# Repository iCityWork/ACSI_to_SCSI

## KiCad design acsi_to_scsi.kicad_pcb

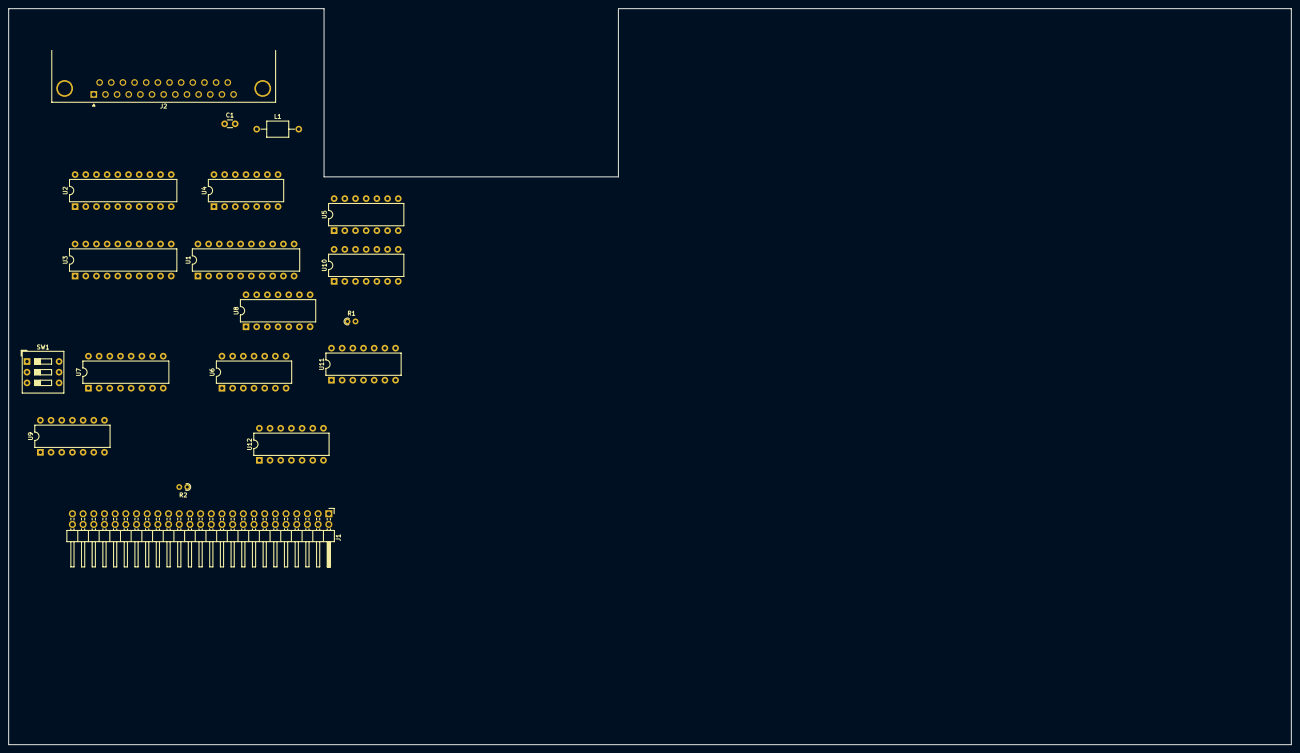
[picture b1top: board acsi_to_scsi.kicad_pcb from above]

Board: 2 copper layers, 305.0 x 175.0 mm, 19 parts (0 on the bottom side), 64 nets, no tracks yet.

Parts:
C1: 27pF; C_Disc_D3.0mm_W1.6mm_P2.50mm
J1: SCSI; PinHeader_2x25_P2.54mm_Horizontal
J2: ACSI; DSUB-25_Female_Horizontal_P2.77x2.84mm_EdgePinOffset7.70mm_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
L1: 220uH; L_Axial_L5.0mm_D3.6mm_P10.00mm_Horizontal_Murata_BL01RN1A2A2
R1: 2.2k; R_Axial_DIN0204_L3.6mm_D1.6mm_P1.90mm_Vertical
R2: 1k; R_Axial_DIN0204_L3.6mm_D1.6mm_P1.90mm_Vertical
SW1: SW_DIP_x03; SW_DIP_SPSTx03_Slide_9.78x9.8mm_W7.62mm_P2.54mm
U1: 74ALS573; DIP-20_W7.62mm
U2, U3: 74ALS540; DIP-20_W7.62mm
U4: 74LS01; DIP-14_W7.62mm
U5, U11: 74ALS74; DIP-14_W7.62mm
U6: 74ALS08; DIP-14_W7.62mm
U7: 74ALS85; DIP-16_W7.62mm
U8: 74LS04; DIP-14_W7.62mm
U9: 74LS08; DIP-14_W7.62mm
U10: 74LS02; DIP-14_W7.62mm
U12: 74LS280; DIP-14_W7.62mm

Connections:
/A1: J2.16, U7.10 (A0)
/ACK: J2.14, U9.13
/D0: J2.1, U1.2 (D0), U2.18 (~B0)
/D1: J2.2, U1.3 (D1), U2.17 (~B1)
/D2: J2.3, U1.4 (D2), U2.16 (~B2)
/D3: J2.4, U1.5 (D3), U2.15 (~B3)
/D4: J2.5, U1.6 (D4), U2.14 (~B4)
/D5: J2.6, U1.7 (D5), U2.13 (~B5)
/D6: J2.7, U1.8 (D6), U2.12 (~B6)
/D7: J2.8, U1.9 (D7), U2.11 (~B7)
/DR: J2.19, U4.1
/IR: J2.10, U4.13
/RESET: C1.1, J2.12, L1.1
/R/W: J2.18, U8.3
/SEL: J2.9, U9.12, U11.11 (C)
GND: C1.2, J1.1, J1.3, J1.5, J1.7, J1.9, J1.11, J1.13, J1.15, J1.17, J1.19, J1.21, J1.23, J1.27, J1.29, J1.31, J1.33, J1.35, J1.37, J1.39, J1.41, J1.43, J1.45, J1.47, J1.49, SW1.4, SW1.5, SW1.6, U1.1 (OE), U1.10 (GND), U2.10 (GND), U3.10 (GND), U4.7 (GND), U5.2 (D), U5.7 (GND), U6.7 (GND), U7.2 (Ia<b), U7.8 (GND), U7.9 (B0), U8.7 (GND), U9.1, U9.2, U9.4, U9.5, U9.7 (GND), U10.7 (GND), U10.8, U10.9, U11.2 (D), U11.7 (GND), U12.4 (I), U12.7 (GND)
unnamed: J1.4, U2.3 (A1), U3.17 (~B1), U12.9 (B)
unnamed: J1.6, U2.4 (A2), U3.16 (~B2), U12.10 (C)
unnamed: J1.8, U2.5 (A3), U3.15 (~B3), U12.11 (D)
unnamed: J1.10, U2.6 (A4), U3.14 (~B4), U12.12 (E)
unnamed: J1.12, U2.7 (A5), U3.13 (~B5), U12.13 (F)
unnamed: J1.14, U2.8 (A6), U3.12 (~B6), U12.1 (G)
unnamed: J1.16, U2.9 (A7), U3.11 (~B7), U12.2 (H)
unnamed: J1.18, U12.6 (Odd)
unnamed: J1.32, R2.2
unnamed: J1.2, J1.36, U2.1 (~G1), U2.2 (A0), U3.1 (~G1), U3.18 (~B0), U4.10, U10.5, U10.6, U12.8 (A)
unnamed: J1.40, U8.8, U11.1 (~R)
unnamed: J1.46, U4.2, U8.13
unnamed: J1.50, U9.9, U9.10
unnamed: U1.11 (Load), U8.1, U9.11, U10.11
unnamed: U1.12 (Q7), U6.4, U7.11 (B1)
unnamed: U1.13 (Q6), U6.12, U7.14 (B2)
unnamed: U1.14 (Q5), U6.1, U7.1 (B3)
unnamed: U1.15 (Q4), U3.6 (A4)
unnamed: U1.16 (Q3), U3.5 (A3)
unnamed: U1.17 (Q2), U3.4 (A2)
unnamed: U1.18 (Q1), U3.3 (A1)
unnamed: U1.19 (Q0), U3.2 (A0)
unnamed: U2.19 (~G2), U7.3 (Ia=b), U8.4
unnamed: U3.7 (A5), U6.3
unnamed: U3.8 (A6), U6.11
unnamed: U3.9 (A7), U6.6
unnamed: R1.2, U4.5, U4.6, U5.10 (~S), U11.10 (~S)
unnamed: U4.3, U4.11, U5.9 (Q)
unnamed: U4.12, U8.12
unnamed: U5.1 (~R), U5.12 (D), U6.8
unnamed: U5.3 (C), U8.2
unnamed: J1.38, U5.5 (Q)
unnamed: J1.42, U6.9
unnamed: SW1.3, U7.12 (A1)
unnamed: SW1.2, U7.13 (A2)
unnamed: SW1.1, U7.15 (A3)
unnamed: U5.4 (~S), U5.11 (C), U8.6
unnamed: U8.9, U8.10, U10.3, U10.12
unnamed: L1.2, U8.11
unnamed: U10.2, U10.4
unnamed: U5.13 (~R), U10.13
unnamed: J1.48, U3.19 (~G2), U8.5, U9.8, U11.3 (C)
unnamed: U6.2, U6.5, U6.10, U6.13, U11.6 (~Q)
unnamed: J1.44, U11.4 (~S), U11.8 (~Q)
unnamed: U4.8, U4.9, U11.9 (Q)
unnamed: U7.6 (Oa=b), U11.12 (D)
unnamed: U10.1, U11.13 (~R)
VCC: J1.26, R1.1, R2.1, U1.20 (VCC), U2.20 (VCC), U3.20 (VCC), U4.14 (VCC), U5.14 (VCC), U6.14 (VCC), U7.16 (VCC), U8.14 (VCC), U9.14 (VCC), U10.14 (VCC), U11.14 (VCC), U12.14 (VCC)

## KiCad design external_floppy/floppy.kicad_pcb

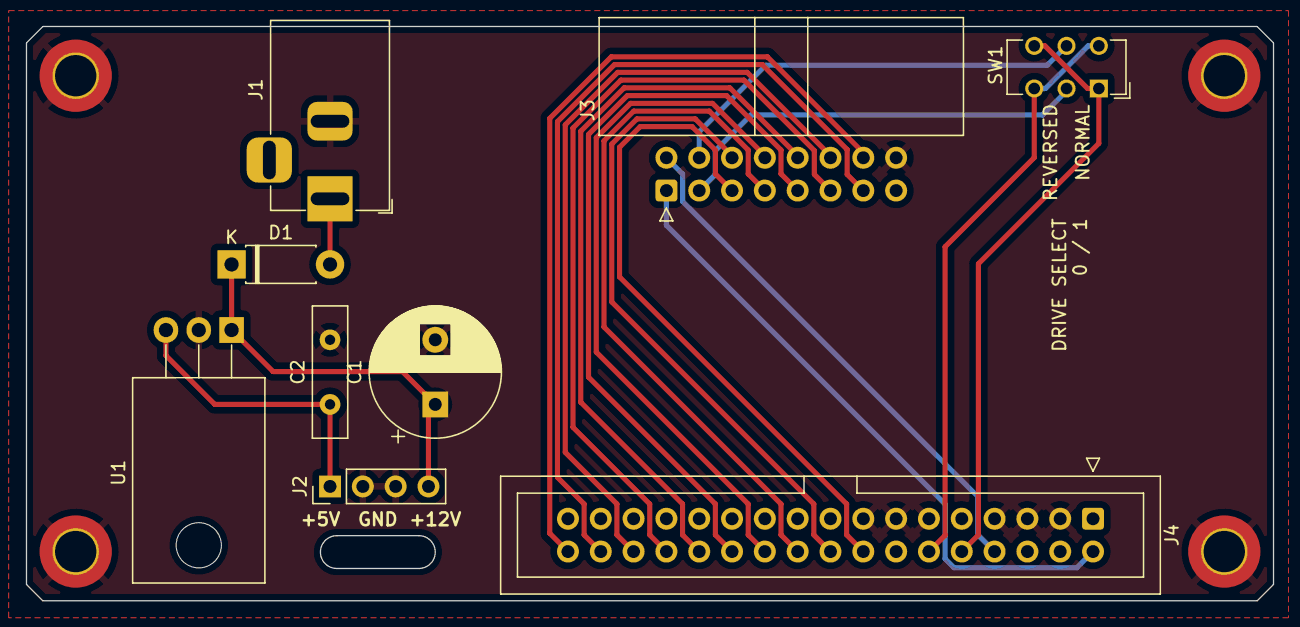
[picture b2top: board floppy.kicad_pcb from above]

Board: 2 copper layers, 96.5 x 44.5 mm, 13 parts (0 on the bottom side), 20 nets.

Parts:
C1: 470uF; CP_Radial_D10.0mm_P5.00mm
C2: 10uF; C_Disc_D10.0mm_W2.5mm_P5.00mm
D1: 1N4007; D_DO-41_SOD81_P7.62mm_Horizontal
H1, H2, H3, H4: MountingHole_Pad; MountingHole_3.2mm_M3_DIN965_Pad_TopBottom
J1: 12VDC; BarrelJack_Horizontal
J2: FLOPPY_PWR; PinHeader_1x04_P2.54mm_Vertical
J3: ADAPTER; IDC-Header_2x08_P2.54mm_Horizontal
J4: FLOPPY; IDC-Header_2x17_P2.54mm_Vertical
SW1: SW_DPDT_x2; SW_CuK_JS202011AQN_DPDT_Angled
U1: L7805; TO-220-3_Horizontal_TabDown

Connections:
+5V: C2.1, J2.1, U1.3 (OUT)
+12V: C1.1, D1.1 (K), J2.4, U1.1 (IN)
/FLOPPY_DISKCHANGE: J3.1, J4.2
/FLOPPY_INDEX: J3.2, J4.8
/FLOPPY_MOTOR_ON: J3.5, J4.16
/FLOPPY_READY: J3.14, J4.34
/FLOPPY_READ_DATA: J3.12, J4.30
/FLOPPY_SELECT_A: J3.3, SW1.2 (B)
/FLOPPY_SELECT_B: J3.4, SW1.5 (B)
/FLOPPY_SIDE_SELECT: J3.13, J4.32
/FLOPPY_STEP: J3.7, J4.20
/FLOPPY_STEP_DIRECTION: J3.6, J4.18
/FLOPPY_TRACK_00: J3.10, J4.26
/FLOPPY_WRITE_DATA: J3.8, J4.22
/FLOPPY_WRITE_GATE: J3.9, J4.24
/FLOPPY_WRITE_PROTECT: J3.11, J4.28
/F_INSEL_A: J4.10, SW1.1 (A), SW1.6 (C)
/F_INSEL_B: J4.12, SW1.3 (C), SW1.4 (A)
GND: C1.2, C2.2, H1.1, H2.1, H3.1, H4.1, J1.2, J2.2, J2.3, J3.16, J4.3, J4.5, J4.7, J4.9, J4.11, J4.13, J4.15, J4.17, J4.19, J4.21, J4.23, J4.25, J4.27, J4.29, J4.31, J4.33, U1.2 (GND)
unnamed: D1.2 (A), J1.1

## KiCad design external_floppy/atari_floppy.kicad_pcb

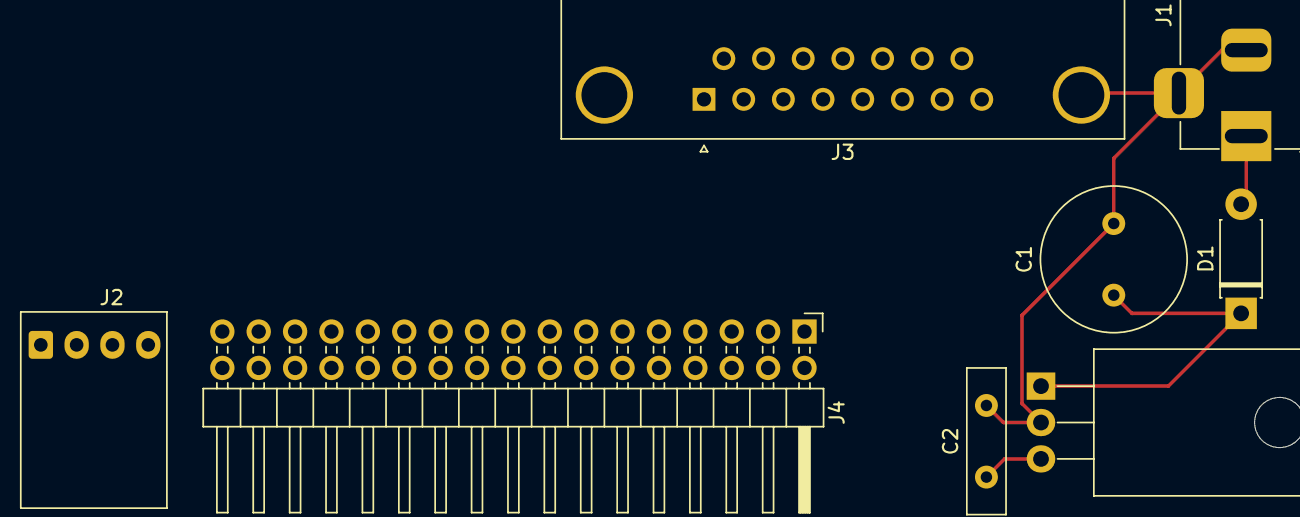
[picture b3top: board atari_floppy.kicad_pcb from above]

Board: 2 copper layers, 8 parts (0 on the bottom side), 15 nets.

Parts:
C1: 470uF; C_Radial_D10.0mm_H12.5mm_P5.00mm
C2: 10uF; C_Disc_D10.0mm_W2.5mm_P5.00mm
D1: 1N4007; D_DO-41_SOD81_P7.62mm_Horizontal
J1: 12VDC; BarrelJack_Horizontal
J2: FLOPPY_PWR; 171826-4
J3: DATA_IN; DSUB-15_Female_Horizontal_P2.77x2.84mm_EdgePinOffset4.94mm_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
J4: FLOPPY; PinHeader_2x17_P2.54mm_Horizontal
U1: L7805; TO-220-3_Horizontal_TabDown

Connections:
+5V: C2.1, J2.1, U1.3
+12V: C1.1, D1.1, J2.4, U1.1
GND: C1.2, C2.2, J1.2, J2.2, J2.3, J3.0, J3.3, J3.7, J4.3, J4.5, J4.7, J4.9, J4.11, J4.13, J4.15, J4.17, J4.19, J4.21, J4.23, J4.25, J4.27, J4.29, J4.31, J4.33, U1.2
unnamed: D1.2, J1.1
unnamed: J3.1, J4.30
unnamed: J3.2, J4.32
unnamed: J3.4, J4.8
unnamed: J3.5, J4.10
unnamed: J3.8, J4.16
unnamed: J3.9, J4.18
unnamed: J3.10, J4.20
unnamed: J3.11, J4.22
unnamed: J3.12, J4.24
unnamed: J3.13, J4.26
unnamed: J3.14, J4.28

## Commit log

2020-11-30 init
2020-12-30 kicad 6 bump
